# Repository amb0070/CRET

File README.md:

CRET - Can Bus Reverse Engineering Toolkit

Author: Adrian Marcos Batlle

# Why another CAN tool?

- Built from scratch with new ideas for analysis mechanisms.
- The unique tool with easy identification and tagging of the packets.
- Comfortable analysis using a GUI.
- Internal project management with SQLite database.
- RAW Sniffing.
- Real-time graphical sniffing.
- Posibility to configure to ignore unuseful packets when sniffing.
- Posibility to split byte values to help identification of the data.
- JSON import and export for identified packets.

# Setup and running:

- Just run .jar file. Custom hardware is needed. You can find gerber files in hardware folder to DIY.

# Features

- 2-Interface support at the same time.
- RAW sniffing on trace mode (shows all packet changes).
- RAW sniffing on monitor mode (updates all packet changes).
- Real-time graphical sniffing.
- Remove option to hide unuseful plotted packets.
- Internal project management with SQLite database.
- Dashboard with identified packets.
- Posibility to import and export JSON files with the identified packets.
- Posibility to ignore unuseful packets (packets with value 00).
- Posibility to split bytes to help identification of the data.
- Threaded sniffing and GUI.
- Clean tabs option for each analysis.
- Comfortable and intuitive GUI.

# Screenshots

 - Data view mode.

 - Analysis mode.

 - Dashboard mode.

 - Real time frame viewer.

# PoC videos

- Analysis mode.

<div align="center">
  
</div>

- Dashboard mode. Demo 1.

<div align="center">
  
</div>

- Dashboard mode. Demo 2.

<div align="center">
  
</div>

# Hardware

 Here are some pictures of the produced hardware:

# License

Copyright (c) 2018 - 2019 Adrian Marcos

This program is free software: you can redistribute it and/or modify it under the terms of the GNU General Public License as published by the Free Software Foundation, either version 3 of the License, or any later version.

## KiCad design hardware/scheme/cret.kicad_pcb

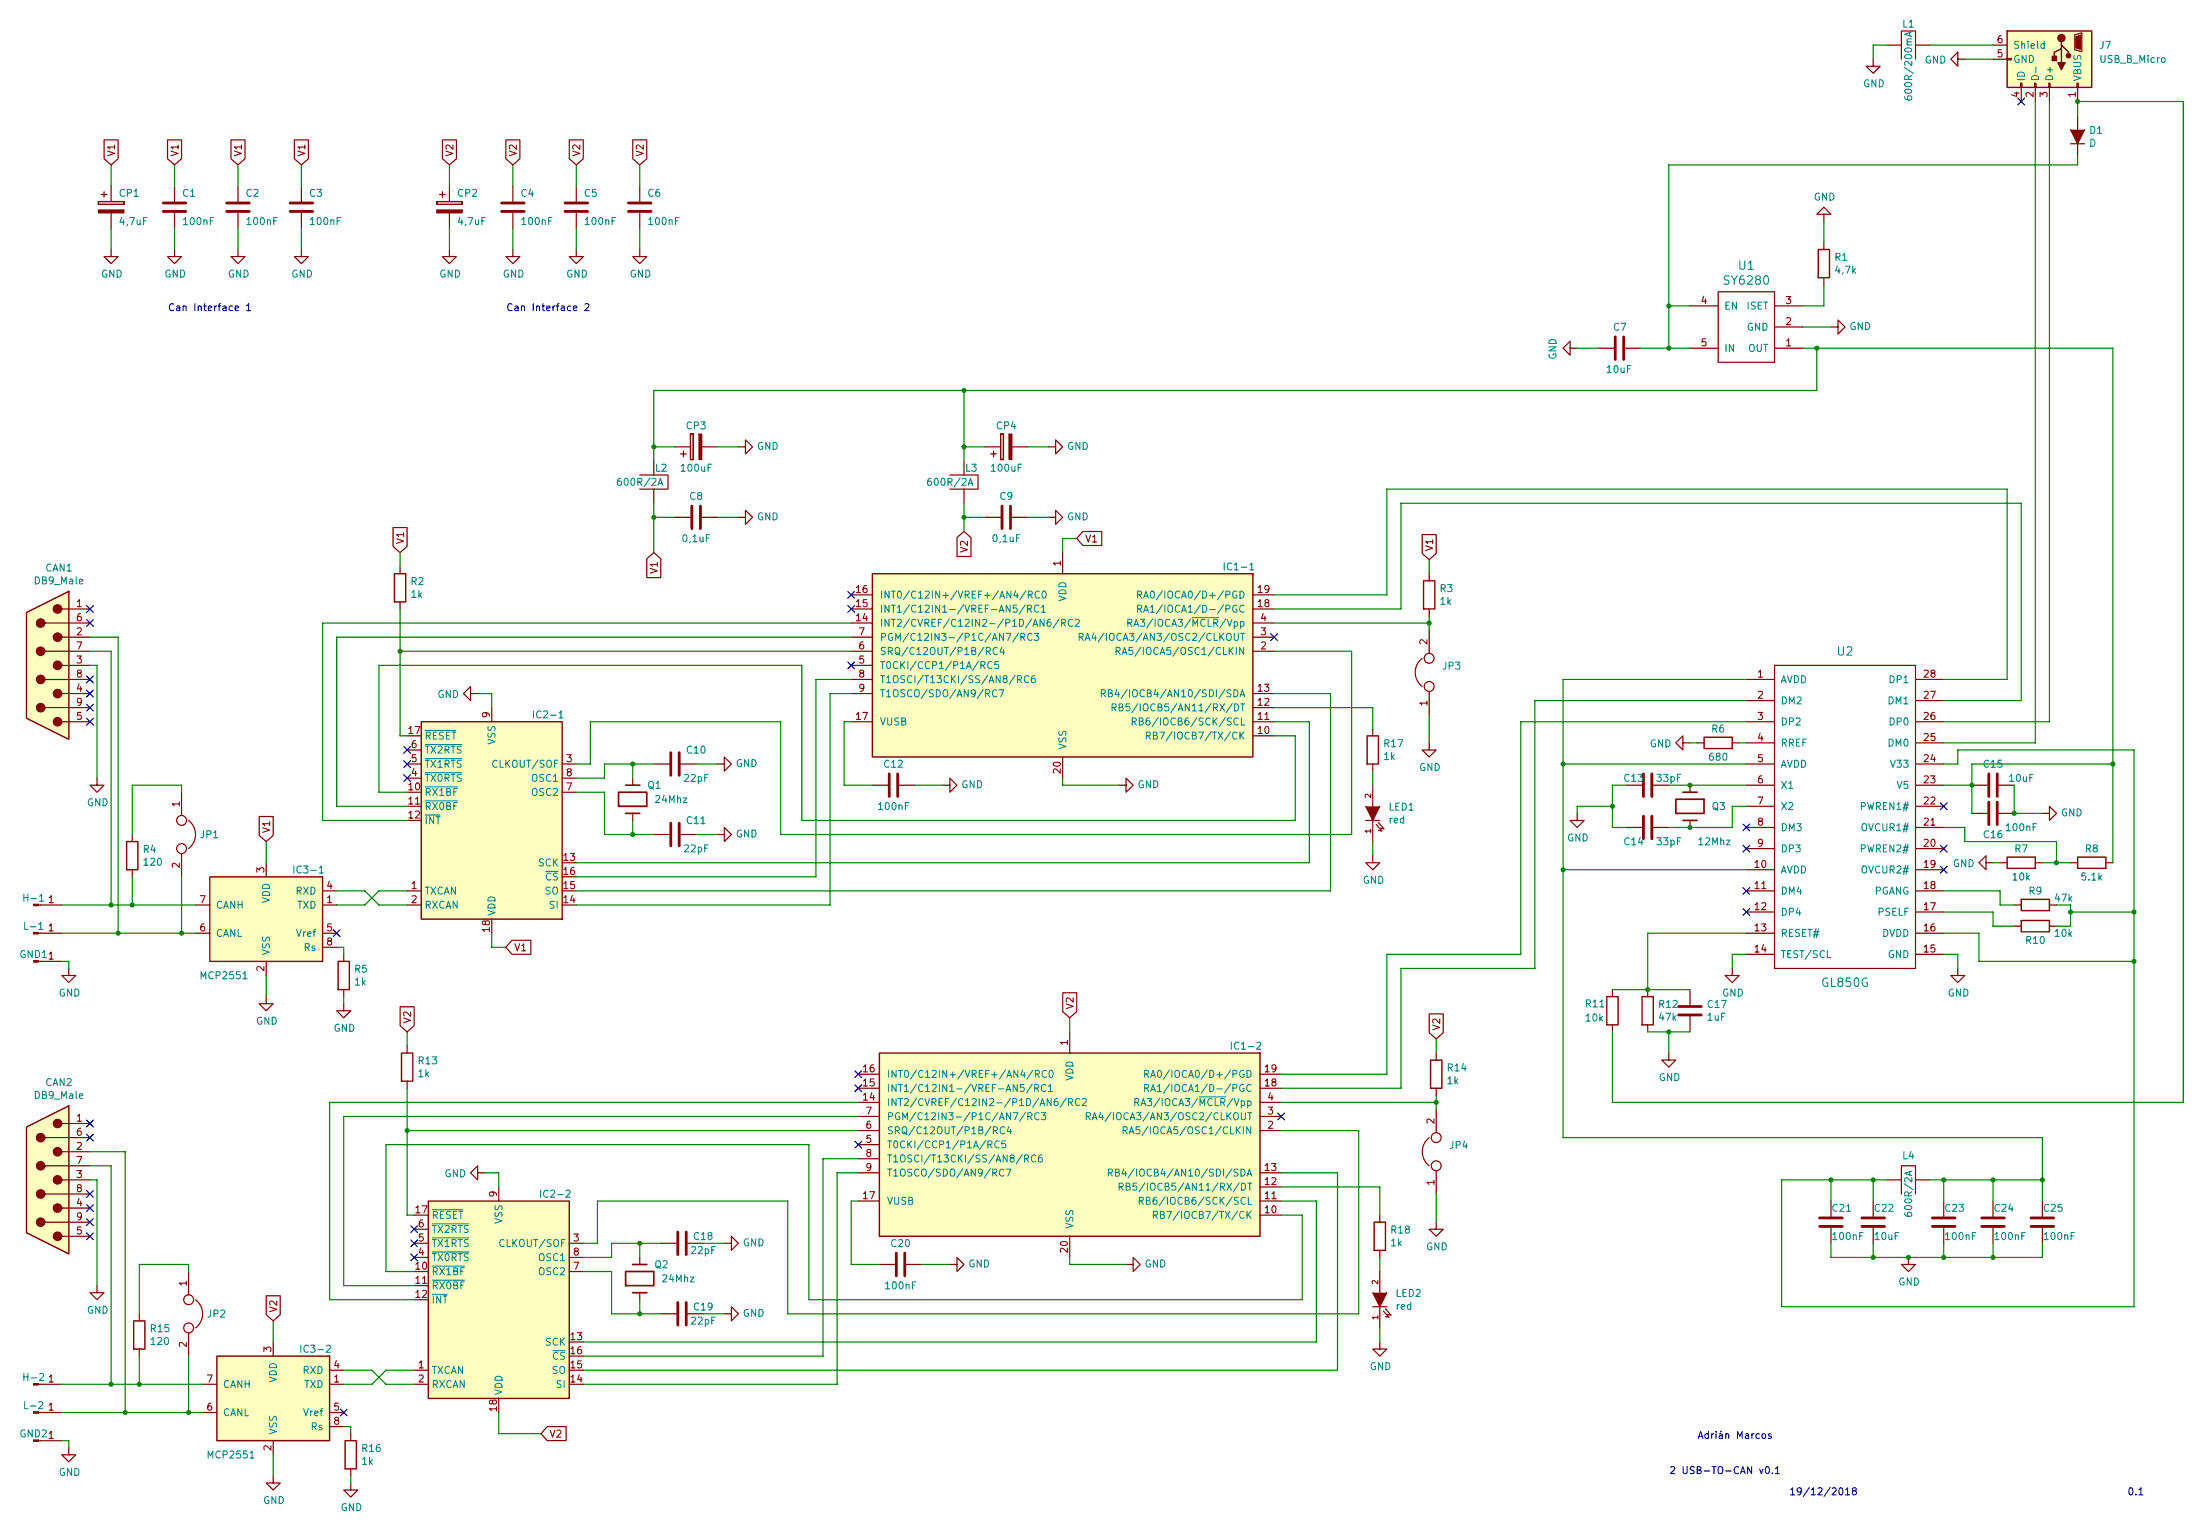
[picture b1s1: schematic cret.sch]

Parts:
C1, C2, C3, C4, C5, C6, C12, C16, C20, C21, C23, C24, C25: 100nF; C_1206_3216Metric_Pad1.42x1.75mm_HandSolder
C7, C15, C22: 10uF; C_1206_3216Metric_Pad1.42x1.75mm_HandSolder
C8, C9: 0,1uF; C_1206_3216Metric_Pad1.42x1.75mm_HandSolder
C10, C11, C18, C19: 22pF; C_1206_3216Metric_Pad1.42x1.75mm_HandSolder
C13, C14: 33pF; C_1206_3216Metric_Pad1.42x1.75mm_HandSolder
C17: 1uF; C_1206_3216Metric_Pad1.42x1.75mm_HandSolder
CAN1, CAN2: DB9_Male; DSUB-9_Male_Horizontal_P2.77x2.84mm_EdgePinOffset4.94mm_Hou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
CP1, CP2: 4,7uF; C_1206_3216Metric_Pad1.42x1.75mm_HandSolder
CP3, CP4: 100uF; C_1206_3216Metric_Pad1.42x1.75mm_HandSolder
D1: D; D_1206_3216Metric_Pad1.42x1.75mm_HandSolder
GND1, GND2: Conn_01x01_Male; TestPoint_Pad_D2.5mm
H-1, H-2: Conn_01x01_Male; TestPoint_Pad_D2.5mm
IC1-1, IC1-2: PIC18F14K50-ESO; SOIC-20W_7.5x12.8mm_P1.27mm
IC2-1, IC2-2: MCP2515-xSO; SOIC-18W_7.5x11.6mm_P1.27mm
IC3-1, IC3-2: MCP2551; SO-8_5.3x6.2mm_P1.27mm
J7: USB_B_Micro; USB_Micro-B_Molex-105017-0001
JP1, JP2, JP3, JP4: JUMPER; TestPoint_2Pads_Pitch2.54mm_Drill0.8mm
L1: 600R/200mA; R_1206_3216Metric_Pad1.42x1.75mm_HandSolder
L2, L3, L4: 600R/2A; R_1206_3216Metric_Pad1.42x1.75mm_HandSolder
L-1, L-2: Conn_01x01_Male; TestPoint_Pad_D2.5mm
LED1, LED2: red; LED_1206_3216Metric_Pad1.42x1.75mm_HandSolder
Q1, Q2: 24Mhz; Crystal_SMD_HC49-SD_HandSoldering
Q3: 12Mhz; Crystal_SMD_HC49-SD_HandSoldering
R1: 4,7k; R_1206_3216Metric_Pad1.42x1.75mm_HandSolder
R2, R3, R5, R13, R14, R16, R17, R18: 1k; R_1206_3216Metric_Pad1.42x1.75mm_HandSolder
R4, R15: 120; R_1206_3216Metric_Pad1.42x1.75mm_HandSolder
R6: 680; R_1206_3216Metric_Pad1.42x1.75mm_HandSolder
R7, R10, R11: 10k; R_1206_3216Metric_Pad1.42x1.75mm_HandSolder
R8: 5.1k; R_1206_3216Metric_Pad1.42x1.75mm_HandSolder
R9, R12: 47k; R_1206_3216Metric_Pad1.42x1.75mm_HandSolder
U1: SY6280; SOT-23-5_HandSoldering
U2: GL850G; SSOP-28_5.3x10.2mm_P0.65mm

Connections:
GND: C1.2, C2.2, C3.2, C4.2, C5.2, C6.2, C7.2, C8.1, C9.1, C10.2, C11.2, C12.2, C13.2, C14.2, C15.2, C16.2, C17.2, C18.2, C19.2, C20.2, C21.2, C22.2, C23.2, C24.2, C25.2, CAN1.3, CAN2.3, CP1.2, CP2.2, CP3.2, CP4.2, GND1.1, GND2.1, IC1-1.20 (VSS), IC1-2.20 (VSS), IC2-1.9 (VSS), IC2-2.9 (VSS), IC3-1.2 (VSS), IC3-2.2 (VSS), J7.5 (GND), JP3.1, JP4.1, L1.1, LED1.1 (K), LED2.1 (K), R1.1, R5.2, R6.1, R7.1, R12.2, R16.2, U1.2 (GND), U2.14 (TEST/SCL), U2.15 (GND); also elsewhere on the board
unnamed: C7.1, D1.1 (K), U1.4 (EN), U1.5 (IN)
unnamed: C10.1, IC2-1.8 (OSC1), Q1.2
unnamed: C11.1, IC2-1.7 (OSC2), Q1.1
unnamed: C12.1, IC1-1.17 (VUSB)
unnamed: C13.1, Q3.1, U2.6 (X1)
unnamed: C14.1, Q3.2, U2.7 (X2)
unnamed: C15.1, C16.1, CP3.1, CP4.1, L2.1, L3.1, R8.2, U1.1 (OUT), U2.23 (V5)
unnamed: C17.1, R11.1, R12.1, U2.13 (RESET#)
unnamed: C18.1, IC2-2.8 (OSC1), Q2.2
unnamed: C19.1, IC2-2.7 (OSC2), Q2.1
unnamed: C20.1, IC1-2.17 (VUSB)
unnamed: C21.1, C22.1, L4.1, R9.1, R10.1, U2.16 (DVDD), U2.24 (V33)
unnamed: C23.1, C24.1, C25.1, L4.2, U2.1 (AVDD), U2.5 (AVDD), U2.10 (AVDD)
unnamed: CAN1.2, IC3-1.6 (CANL), JP1.2, L-1.1
unnamed: CAN1.7, H-1.1, IC3-1.7 (CANH), R4.2
unnamed: CAN2.2, IC3-2.6 (CANL), JP2.2, L-2.1
unnamed: CAN2.7, H-2.1, IC3-2.7 (CANH), R15.2
unnamed: D1.2 (A), J7.1 (VBUS), R11.2
unnamed: IC1-1.2 (RA5/IOCA5/OSC1/CLKIN), IC2-1.3 (CLKOUT/SOF)
unnamed: IC1-1.4 (RA3/IOCA3/~MCLR~/Vpp), JP3.2, R3.2
unnamed: IC1-1.6 (SRQ/C12OUT/P1B/RC4), IC2-1.17 (~RESET), R2.2
unnamed: IC1-1.7 (PGM/C12IN3-/P1C/AN7/RC3), IC2-1.11 (~RX0BF)
unnamed: IC1-1.8 (T1OSCI/T13CKI/SS/AN8/RC6), IC2-1.16 (~CS)
unnamed: IC1-1.9 (T1OSCO/SDO/AN9/RC7), IC2-1.14 (SI)
unnamed: IC1-1.10 (RB7/IOCB7/TX/CK), IC2-1.10 (~RX1BF)
unnamed: IC1-1.11 (RB6/IOCB6/SCK/SCL), IC2-1.13 (SCK)
unnamed: IC1-1.12 (RB5/IOCB5/AN11/RX/DT), R17.1
unnamed: IC1-1.13 (RB4/IOCB4/AN10/SDI/SDA), IC2-1.15 (SO)
unnamed: IC1-1.14 (INT2/CVREF/C12IN2-/P1D/AN6/RC2), IC2-1.12 (~INT)
unnamed: IC1-1.18 (RA1/IOCA1/D-/PGC), U2.27 (DM1)
unnamed: IC1-1.19 (RA0/IOCA0/D+/PGD), U2.28 (DP1)
unnamed: IC1-2.2 (RA5/IOCA5/OSC1/CLKIN), IC2-2.3 (CLKOUT/SOF)
unnamed: IC1-2.4 (RA3/IOCA3/~MCLR~/Vpp), JP4.2, R14.2
unnamed: IC1-2.6 (SRQ/C12OUT/P1B/RC4), IC2-2.17 (~RESET), R13.2
unnamed: IC1-2.7 (PGM/C12IN3-/P1C/AN7/RC3), IC2-2.11 (~RX0BF)
unnamed: IC1-2.8 (T1OSCI/T13CKI/SS/AN8/RC6), IC2-2.16 (~CS)
unnamed: IC1-2.9 (T1OSCO/SDO/AN9/RC7), IC2-2.14 (SI)
unnamed: IC1-2.10 (RB7/IOCB7/TX/CK), IC2-2.10 (~RX1BF)
unnamed: IC1-2.11 (RB6/IOCB6/SCK/SCL), IC2-2.13 (SCK)
unnamed: IC1-2.12 (RB5/IOCB5/AN11/RX/DT), R18.1
unnamed: IC1-2.13 (RB4/IOCB4/AN10/SDI/SDA), IC2-2.15 (SO)
unnamed: IC1-2.14 (INT2/CVREF/C12IN2-/P1D/AN6/RC2), IC2-2.12 (~INT)
unnamed: IC1-2.18 (RA1/IOCA1/D-/PGC), U2.2 (DM2)
unnamed: IC1-2.19 (RA0/IOCA0/D+/PGD), U2.3 (DP2)
unnamed: IC2-1.1 (TXCAN), IC3-1.1 (TXD)
unnamed: IC2-1.2 (RXCAN), IC3-1.4 (RXD)
unnamed: IC2-2.1 (TXCAN), IC3-2.1 (TXD)
unnamed: IC2-2.2 (RXCAN), IC3-2.4 (RXD)
unnamed: IC3-1.8 (Rs), R5.1
unnamed: IC3-2.8 (Rs), R16.1
unnamed: J7.2 (D-), U2.25 (DM0)
unnamed: J7.3 (D+), U2.26 (DP0)
unnamed: J7.6 (Shield), L1.2
unnamed: JP1.1, R4.1
unnamed: JP2.1, R15.1
unnamed: LED1.2 (A), R17.2
unnamed: LED2.2 (A), R18.2
unnamed: R1.2, U1.3 (ISET)
unnamed: R6.2, U2.4 (RREF)
unnamed: R7.2, R8.1, U2.21 (OVCUR1#)
unnamed: R9.2, U2.18 (PGANG)
unnamed: R10.2, U2.17 (PSELF)
V1: C1.1, C2.1, C3.1, C8.2, CP1.1, IC1-1.1 (VDD), IC2-1.18 (VDD), IC3-1.3 (VDD), L2.2, R2.1, R3.1
V2: C4.1, C5.1, C6.1, C9.2, CP2.1, IC1-2.1 (VDD), IC2-2.18 (VDD), IC3-2.3 (VDD), L3.2, R13.1, R14.1

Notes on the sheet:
2 USB-TO-CAN v0.1
Can Interface 1
Can Interface 2
19/12/2018
Adrián Marcos
0.1

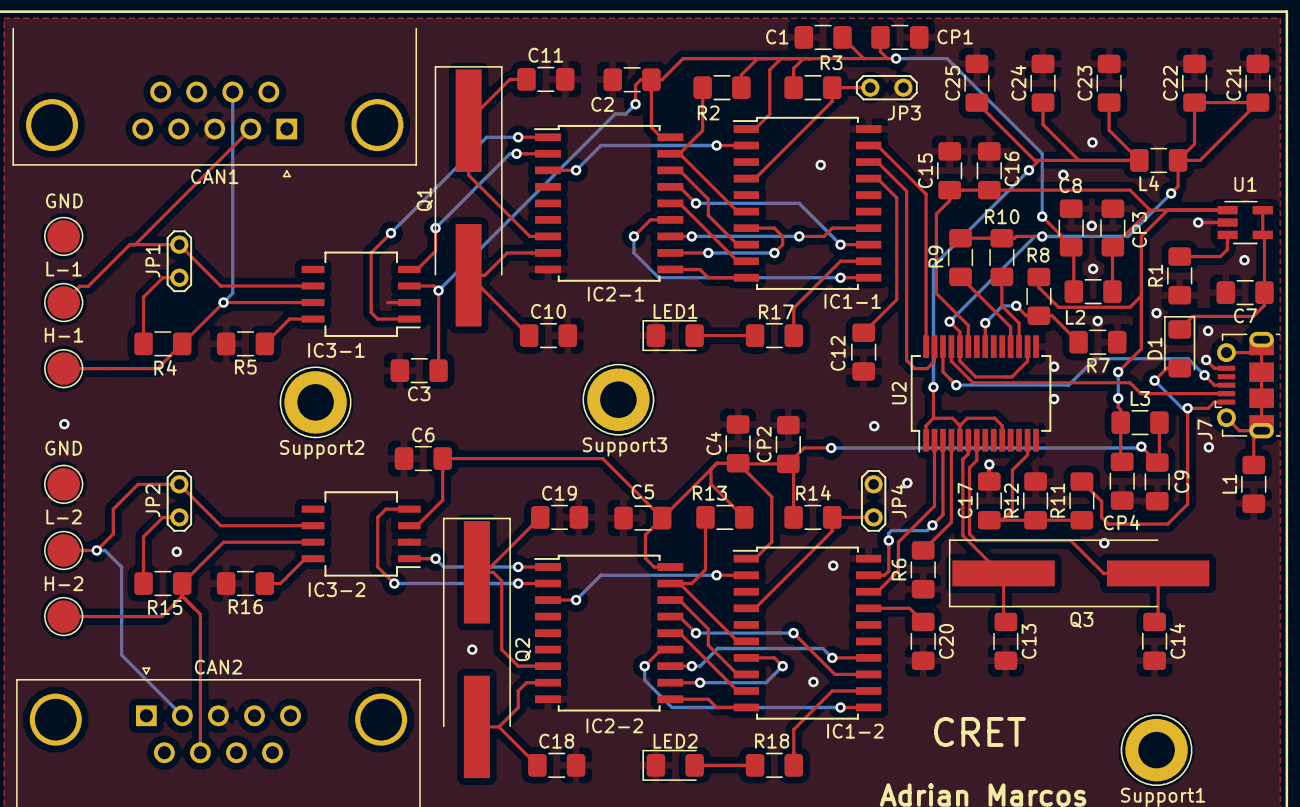
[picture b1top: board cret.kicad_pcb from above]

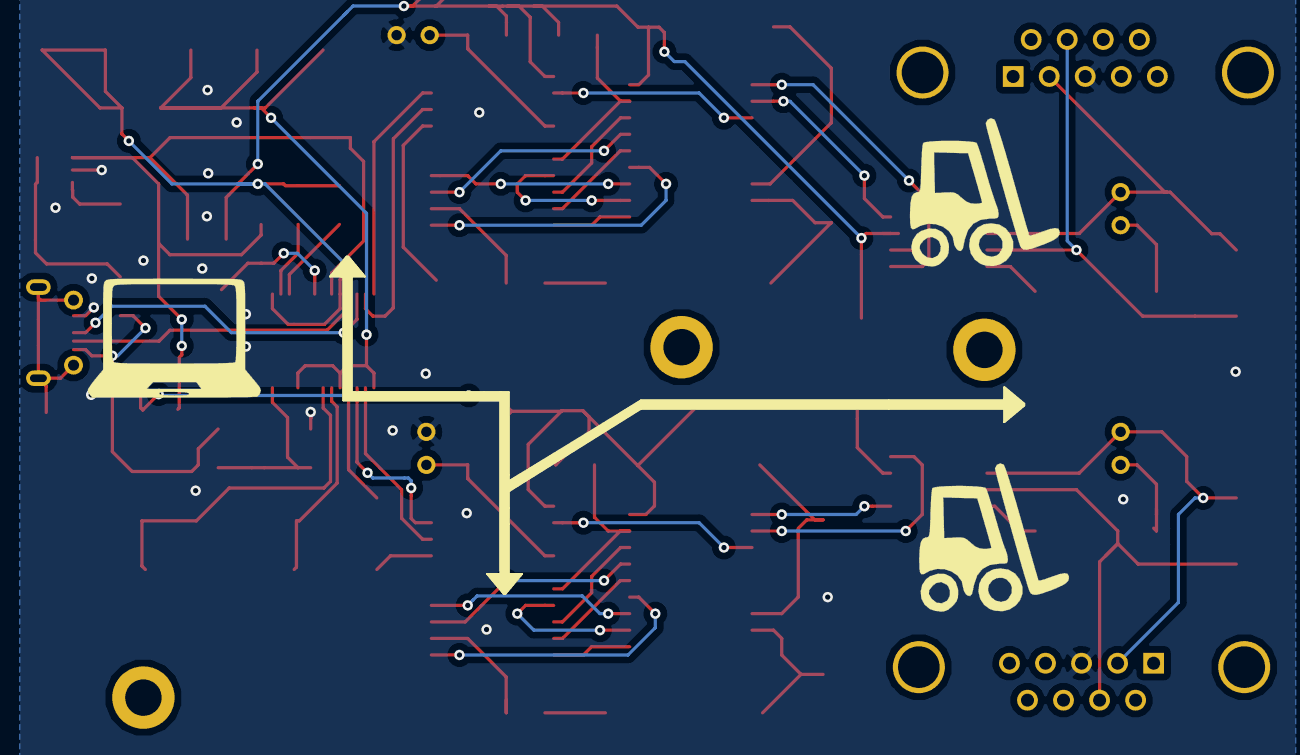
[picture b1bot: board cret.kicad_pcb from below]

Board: 2 copper layers, 85 parts (4 on the bottom side), 65 nets.

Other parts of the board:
G1, G2: LOGO; forklift
G3: CANBUS
G4: LOGO; pc
GND: Conn_01x01_Male; TestPoint_Pad_D2.5mm
GND#2: Conn_01x01_Male; TestPoint_Pad_D2.5mm
Support1, Support2, Support3: TestPoint_Loop_D3.80mm_Drill2.8mm

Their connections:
GND: GND.1, GND#2.1; also elsewhere on the board

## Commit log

2018-12-03 First commit
    Java main application and main graphical interface.
2018-12-05 Database connections and utils
    Classes for database connections. Not finished.
2018-12-05 CanBus and serial port classes
    Canbus connection class and serial port searcher. Not finished.
2018-12-07 Configuration and new project windows
    FXML and controllers of new project and configuration windows. Not finished.
2018-12-08 CAN classes
    CAN classes for receiveing messages
2018-12-08 Updated main and new GUI utils
    Updated main class with a thread for can connection. Only for testing.
2018-12-09 Hardware schemes
    Hardware scheme of 2 can interfaces pcb.
2018-12-13 Finished scheme
    Scheme finished. Netlist generated. ToDo: place elements in the PCB
2018-12-18 Hardware finished
    Scheme reviewed and finished. PCB reviewed and finished. Generated netlist and gerber files. The PCB has been ordered.
2018-12-24 Json and project manager classes
    Initial json and project management classes.
2018-12-24 Main screen. Dynamic line chart generation.
    Main screen updates on FXML file. Also dynamic line chart creation on the FXML GUI.
2018-12-25 Json example file with more than one project.
    Basic json structure for project management.
2018-12-27 Basic structure modfiications
2018-12-27 Project management
    Project management classes
2019-01-07 Database checker
    Database class to check if database exists when the app loads.
2019-01-07 Project classes
    Updated project manager classes
2019-01-07 implemented listener for CAN
    Added the listener that gets the messages from CAN network and stores it in the data structures to be read after.
2019-01-09 Documentation of the project
    Latex documentation of the project
2019-01-10 Added project lister window
    Added the FXML document and event manager of the window to list projects.
2019-01-10 Update of new project window
    Update of the controller and the FXML document of new project window.
2019-01-11 Updated and renamed CAN classes
    Package renamed, classes renamed for CAN classes.
2019-01-11 Window to see graph data RAW
    Window to see the data in RAW mode of one of the selected nodes and bytes. Added a button on each linechart to open it.
2019-01-12 FXML and controller of frame viewer
    FXML Document and the controller of te frame viewer window
2019-01-12 Alert class
    Class to generate messages in the whole project.
2019-01-12 Updated FXML of main window
    Update of the FXML document for main window
2019-01-13 Updated main window controller.
    Dynamic generation of the data structures neccesary to store the data needed to plot. Also dynamic genration of the graphical interfaces.
2019-01-13 Update of the documentation
2019-01-16 Updated CAN classes
    Added option to filter ids from a project.
2019-01-16 File name changes
    Changed filenames of configruation window. Also added comments in the java class.
2019-01-16 Update RootViewController
    Update rootviewcontroller class. Not finished.
2019-01-17 EditableLabel class
    EditableLabel class used to change the name of an assigned node-byte in dashboard.
2019-01-17 Images for the GUI
    Icons and images for the GUI
2019-01-17 Update of CAN classes
    Added listeners for differnti situations. For analyze, dashboard and RAW view.
2019-01-17 Update CAN classes
2019-01-17 Update of database classes
2019-01-17 Create structures.java
    Static class to store data in different structures.
2019-01-17 Update project.java
    Updated project class
2019-01-17 LOGOS
2019-01-17 Update logo
2019-01-17 Update of doc
2019-01-18 Documentation update
2019-01-19 Update on CAN classes
    Updated can classes, changed some elements in rootviewcontroller that affects to this classes.
2019-01-19 Name change
    Changed the name of the main FXML document.
2019-01-19 Update of RootViewController
    Added some comments, finally renamed FXML elements and FXML events.
2019-01-20 Documentation updated
2019-01-22 Documentation update
    Added pictures and more text.
2019-01-22 Updated doc
2019-01-23 Commented and updated structures
2019-01-30 JSON File importer
    JSON File parser to import projects.
2019-01-30 JSON File export
    Export projects in JSON format.
2019-01-30 Update CanConnection.java
    Commented and removed unnecesary code.
2019-01-30 Update CanTable.java
    Commented and removed unnecessary code.
2019-01-30 Update CanUtils.java
    Commented and removed unnecessary code.
2019-01-30 Update DbUtils.java
    Commented and removed unnecessary code.
2019-01-30 Added about window
    Controller and viewer for about window.
2019-01-30 Update ConfigurationViewController.java
    Commented code.
2019-01-30 Update GuiUtils.java
    Commented code.
2019-01-31 Project management window
    Added options to open, import, export and delete projects. Commented code and removed unnecessary functions.
2019-02-05 Anexos
2019-02-05 Update of anexos
2019-02-06 Update of anexos.
2019-02-06 Update of memoria
2019-02-12 Update of documentation
2019-02-13 Added comments to classes
2019-02-13 Added comments to db classes
2019-02-14 Update of anexos
    final version
2019-02-14 Updated comments
    Updated comments from classes.
2019-02-14 Update of comments
    Commented classes. Deleted old class.
2019-02-14 Updated code
2019-02-14 Update ConfigurationViewController.java
    Bug fixed
2019-02-14 JavaDoc
2019-02-15 Create LICENSE
